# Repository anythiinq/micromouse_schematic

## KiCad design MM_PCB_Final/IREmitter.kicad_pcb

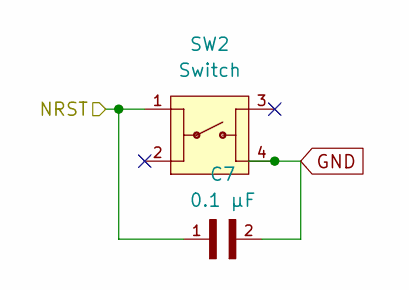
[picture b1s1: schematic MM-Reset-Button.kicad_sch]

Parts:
C7: 0.1 µF; CAPC2012X95N
SW2: Switch; SW_4-1437565-2; PARTREV V

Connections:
/MM-MCU/NRST: C7.1, SW2.1; also elsewhere on the board

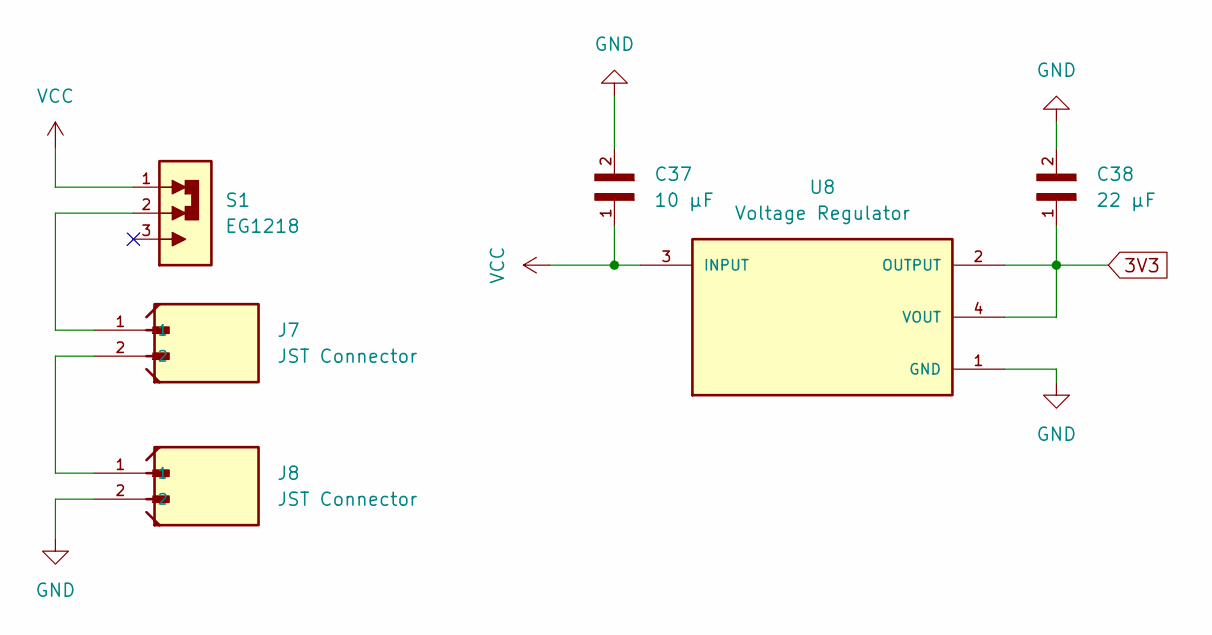
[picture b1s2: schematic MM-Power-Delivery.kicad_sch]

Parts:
C37: 10 µF; CAPC2012X140N
C38: 22 µF; CAPC2012X95N
J7, J8: JST Connector; JST_B2B-PH-K-S
S1: EG1218; SW_EG1218; DigiKey_Part_Number EG1903-ND
U8: Voltage Regulator; SOT230P700X185-4N; PARTREV 2-2

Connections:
3V3: C38.1, U8.2 (OUTPUT), U8.4 (VOUT); also elsewhere on the board
unnamed: J7.1, S1.2
unnamed: J7.2, J8.1
VCC: C37.1, S1.1, U8.3 (INPUT); also elsewhere on the board

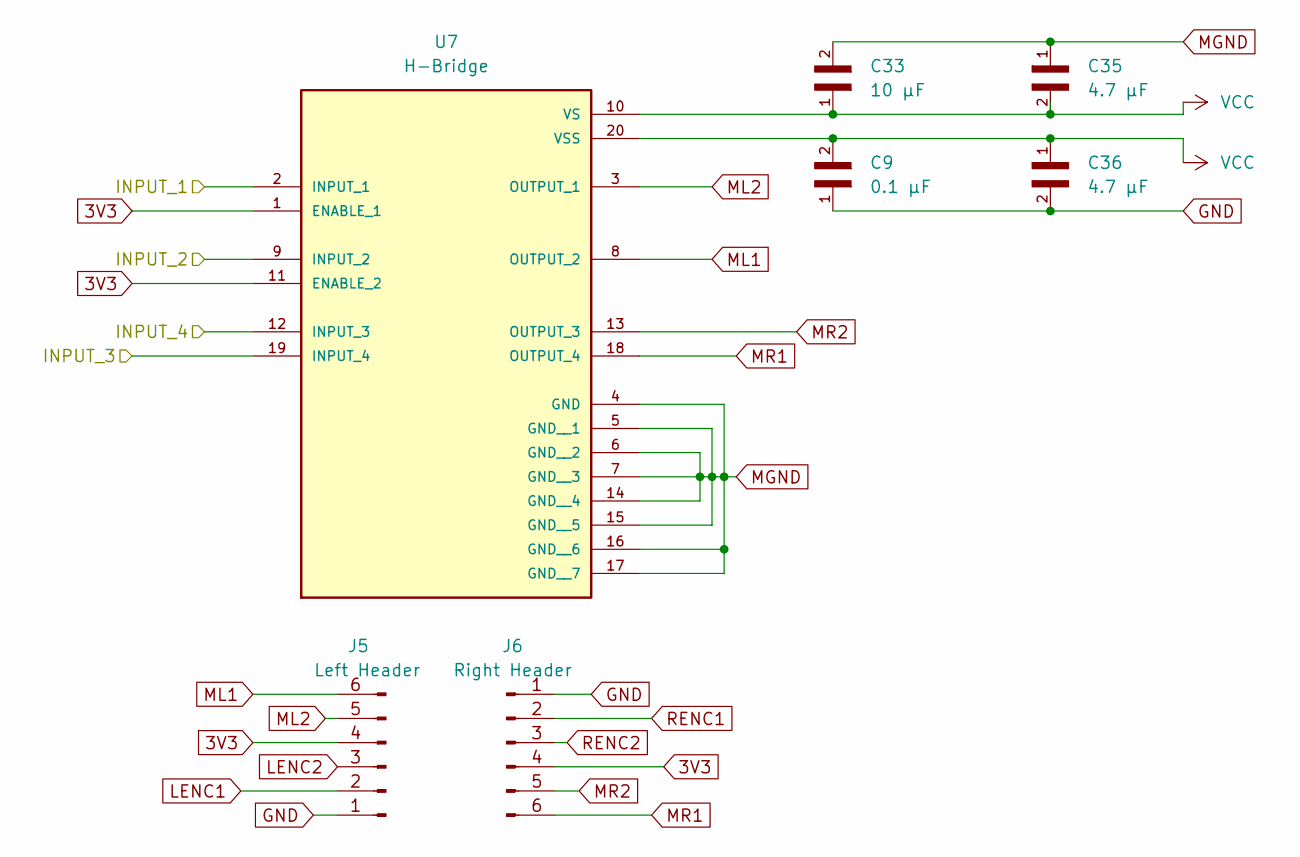
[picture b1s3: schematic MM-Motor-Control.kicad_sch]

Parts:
C9: 0.1 µF; CAPC2012X95N
C33: 10 µF; CAPC2012X140N
C35, C36: 4.7 µF; CAPC2012X140N
J5: Left Header; PinHeader_1x06_P1.27mm_Vertical_SMD_Pin1Left
J6: Right Header; PinHeader_1x06_P1.27mm_Vertical_SMD_Pin1Right
U7: H-Bridge; SOIC127P1032X265-20N; PARTREV N/A

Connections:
3V3: J5.4, J6.4, U7.1 (ENABLE_1), U7.11 (ENABLE_2); also elsewhere on the board
/MM-MCU/INPUT_1: U7.2 (INPUT_1); also elsewhere on the board
/MM-MCU/INPUT_2: U7.9 (INPUT_2); also elsewhere on the board
/MM-MCU/INPUT_3: U7.19 (INPUT_4); also elsewhere on the board
/MM-MCU/INPUT_4: U7.12 (INPUT_3); also elsewhere on the board
ML1: J5.6, U7.8 (OUTPUT_2); also elsewhere on the board
ML2: J5.5, U7.3 (OUTPUT_1); also elsewhere on the board
MR1: J6.6, U7.18 (OUTPUT_4); also elsewhere on the board
MR2: J6.5, U7.13 (OUTPUT_3); also elsewhere on the board
VCC: C9.2, C33.1, C35.2, C36.1, U7.10 (VS), U7.20 (VSS); also elsewhere on the board

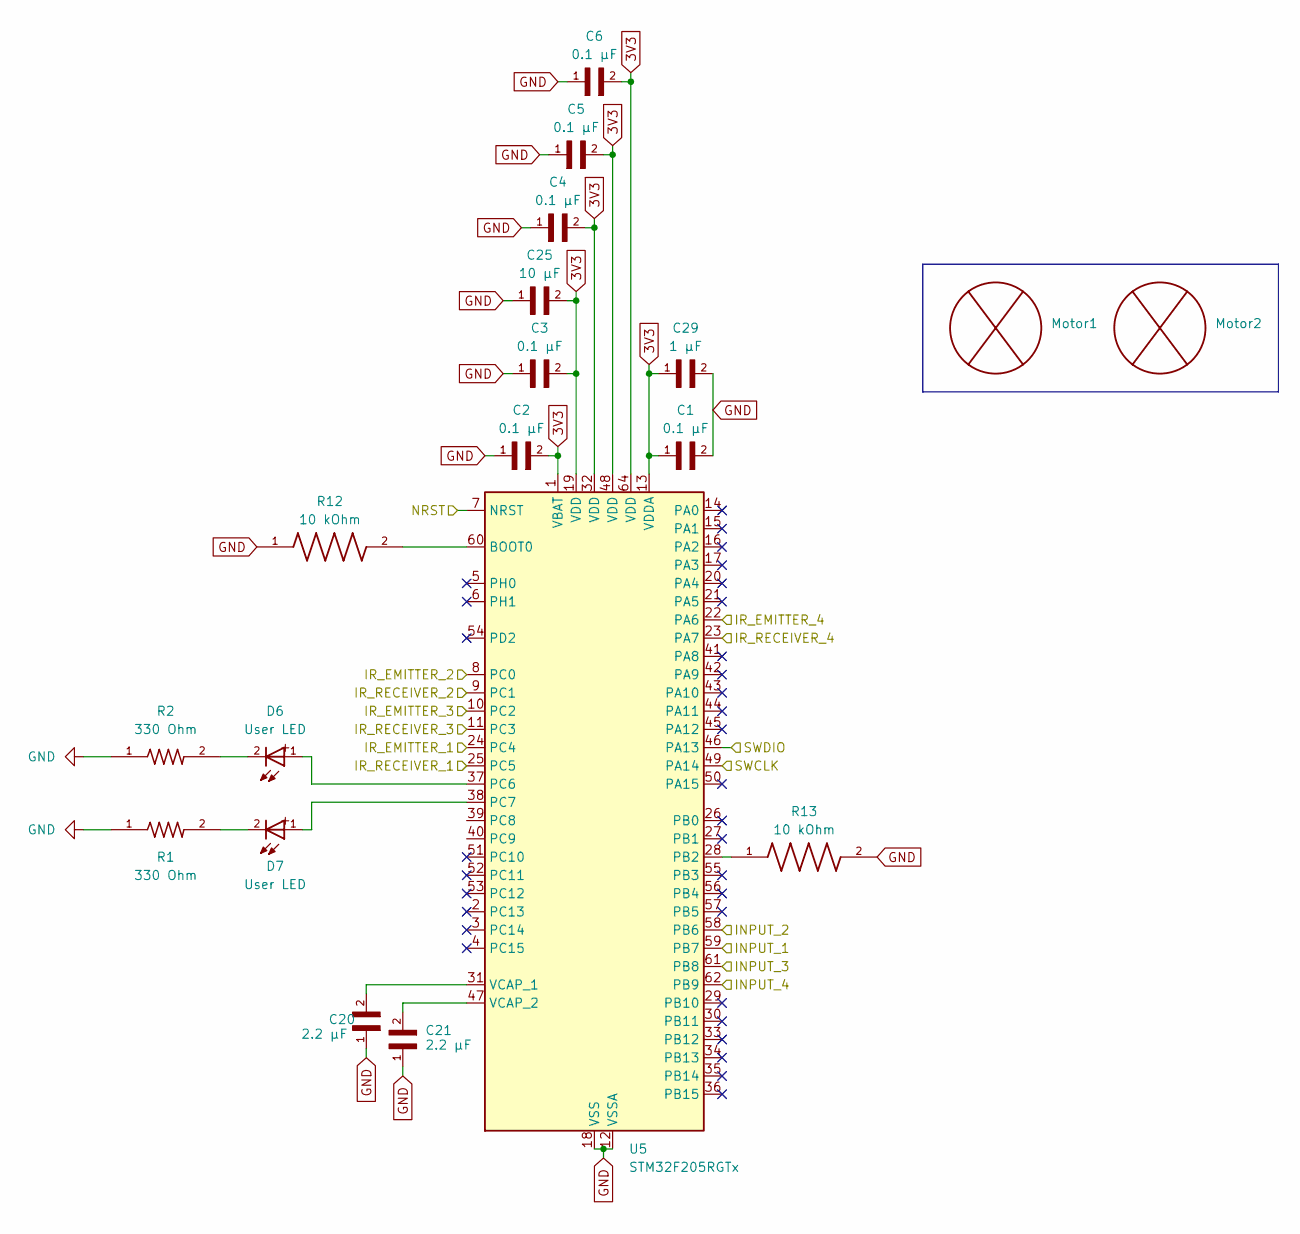
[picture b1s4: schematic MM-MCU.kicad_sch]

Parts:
C1, C2, C3, C4, C5, C6: 0.1 µF; CAPC2012X95N
C20, C21: 2.2 µF; CAPC2012X140N
C25: 10 µF; CAPC2012X140N
C29: 1 µF; CAPC1608X90N
D6, D7: User LED; WL-TMRC_5MM
Motor1, Motor2: Pololu_Motor
R1, R2: 330 Ohm; RESC1607X60N; DigiKey_Part_Number 311-330HRCT-ND
R12, R13: 10 kOhm; RESC2012X65N
U5: STM32F205RGTx; LQFP-64_10x10mm_P0.5mm

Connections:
3V3: C1.1, C2.2, C3.2, C4.2, C5.2, C6.2, C25.2, C29.1, U5.1 (VBAT), U5.13 (VDDA), U5.19 (VDD), U5.32 (VDD), U5.48 (VDD), U5.64 (VDD); also elsewhere on the board
/MM-IR-Emitter/IR_EMITTER_1: U5.24 (PC4); also elsewhere on the board
/MM-IR-Emitter/IR_EMITTER_2: U5.8 (PC0); also elsewhere on the board
/MM-IR-Emitter/IR_EMITTER_3: U5.10 (PC2); also elsewhere on the board
/MM-IR-Emitter/IR_EMITTER_4: U5.22 (PA6); also elsewhere on the board
/MM-IR-Receiver/IR_RECEIVER_1: U5.25 (PC5); also elsewhere on the board
/MM-IR-Receiver/IR_RECEIVER_2: U5.9 (PC1); also elsewhere on the board
/MM-IR-Receiver/IR_RECEIVER_3: U5.11 (PC3); also elsewhere on the board
/MM-IR-Receiver/IR_RECEIVER_4: U5.23 (PA7); also elsewhere on the board
/MM-MCU/INPUT_1: U5.59 (PB7); also elsewhere on the board
/MM-MCU/INPUT_2: U5.58 (PB6); also elsewhere on the board
/MM-MCU/INPUT_3: U5.61 (PB8); also elsewhere on the board
/MM-MCU/INPUT_4: U5.62 (PB9); also elsewhere on the board
/MM-MCU/NRST: U5.7 (NRST); also elsewhere on the board
/MM-MCU/SWCLK: U5.49 (PA14); also elsewhere on the board
/MM-MCU/SWDIO: U5.46 (PA13); also elsewhere on the board
unnamed: D6.2, R2.2
unnamed: D7.2, R1.2
unnamed: R12.2, U5.60 (BOOT0)
unnamed: R13.1, U5.28 (PB2)
unnamed: D6.1, U5.37 (PC6)
unnamed: D7.1, U5.38 (PC7)
unnamed: C20.2, U5.31 (VCAP_1)
unnamed: C21.2, U5.47 (VCAP_2)

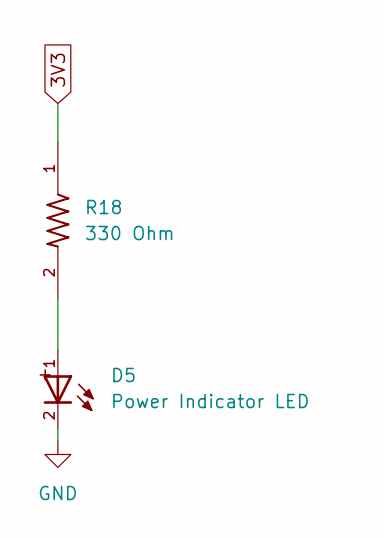
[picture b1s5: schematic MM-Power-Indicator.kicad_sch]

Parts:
D5: Power Indicator LED; WL-TMRC_5MM
R18: 330 Ohm; RESC1607X60N; DigiKey_Part_Number 311-330HRCT-ND

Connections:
3V3: R18.1; also elsewhere on the board
unnamed: D5.1, R18.2

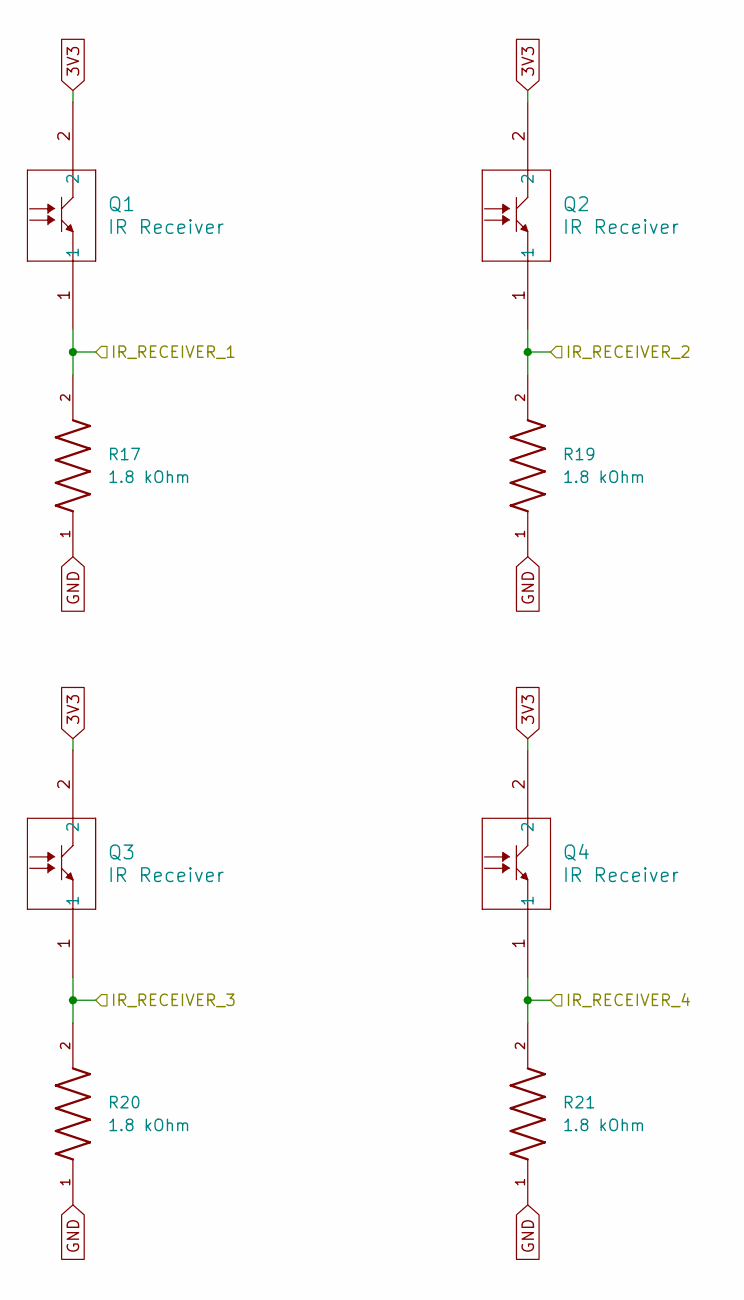
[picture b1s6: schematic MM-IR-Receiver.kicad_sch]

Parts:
Q1, Q2, Q3, Q4: IR Receiver; NoneP157X157-2_LTO
R17, R19, R20, R21: 1.8 kOhm; RESC2012X65N

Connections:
3V3: Q1.2, Q2.2, Q3.2, Q4.2; also elsewhere on the board
/MM-IR-Receiver/IR_RECEIVER_1: Q1.1, R17.2; also elsewhere on the board
/MM-IR-Receiver/IR_RECEIVER_2: Q2.1, R19.2; also elsewhere on the board
/MM-IR-Receiver/IR_RECEIVER_3: Q3.1, R20.2; also elsewhere on the board
/MM-IR-Receiver/IR_RECEIVER_4: Q4.1, R21.2; also elsewhere on the board

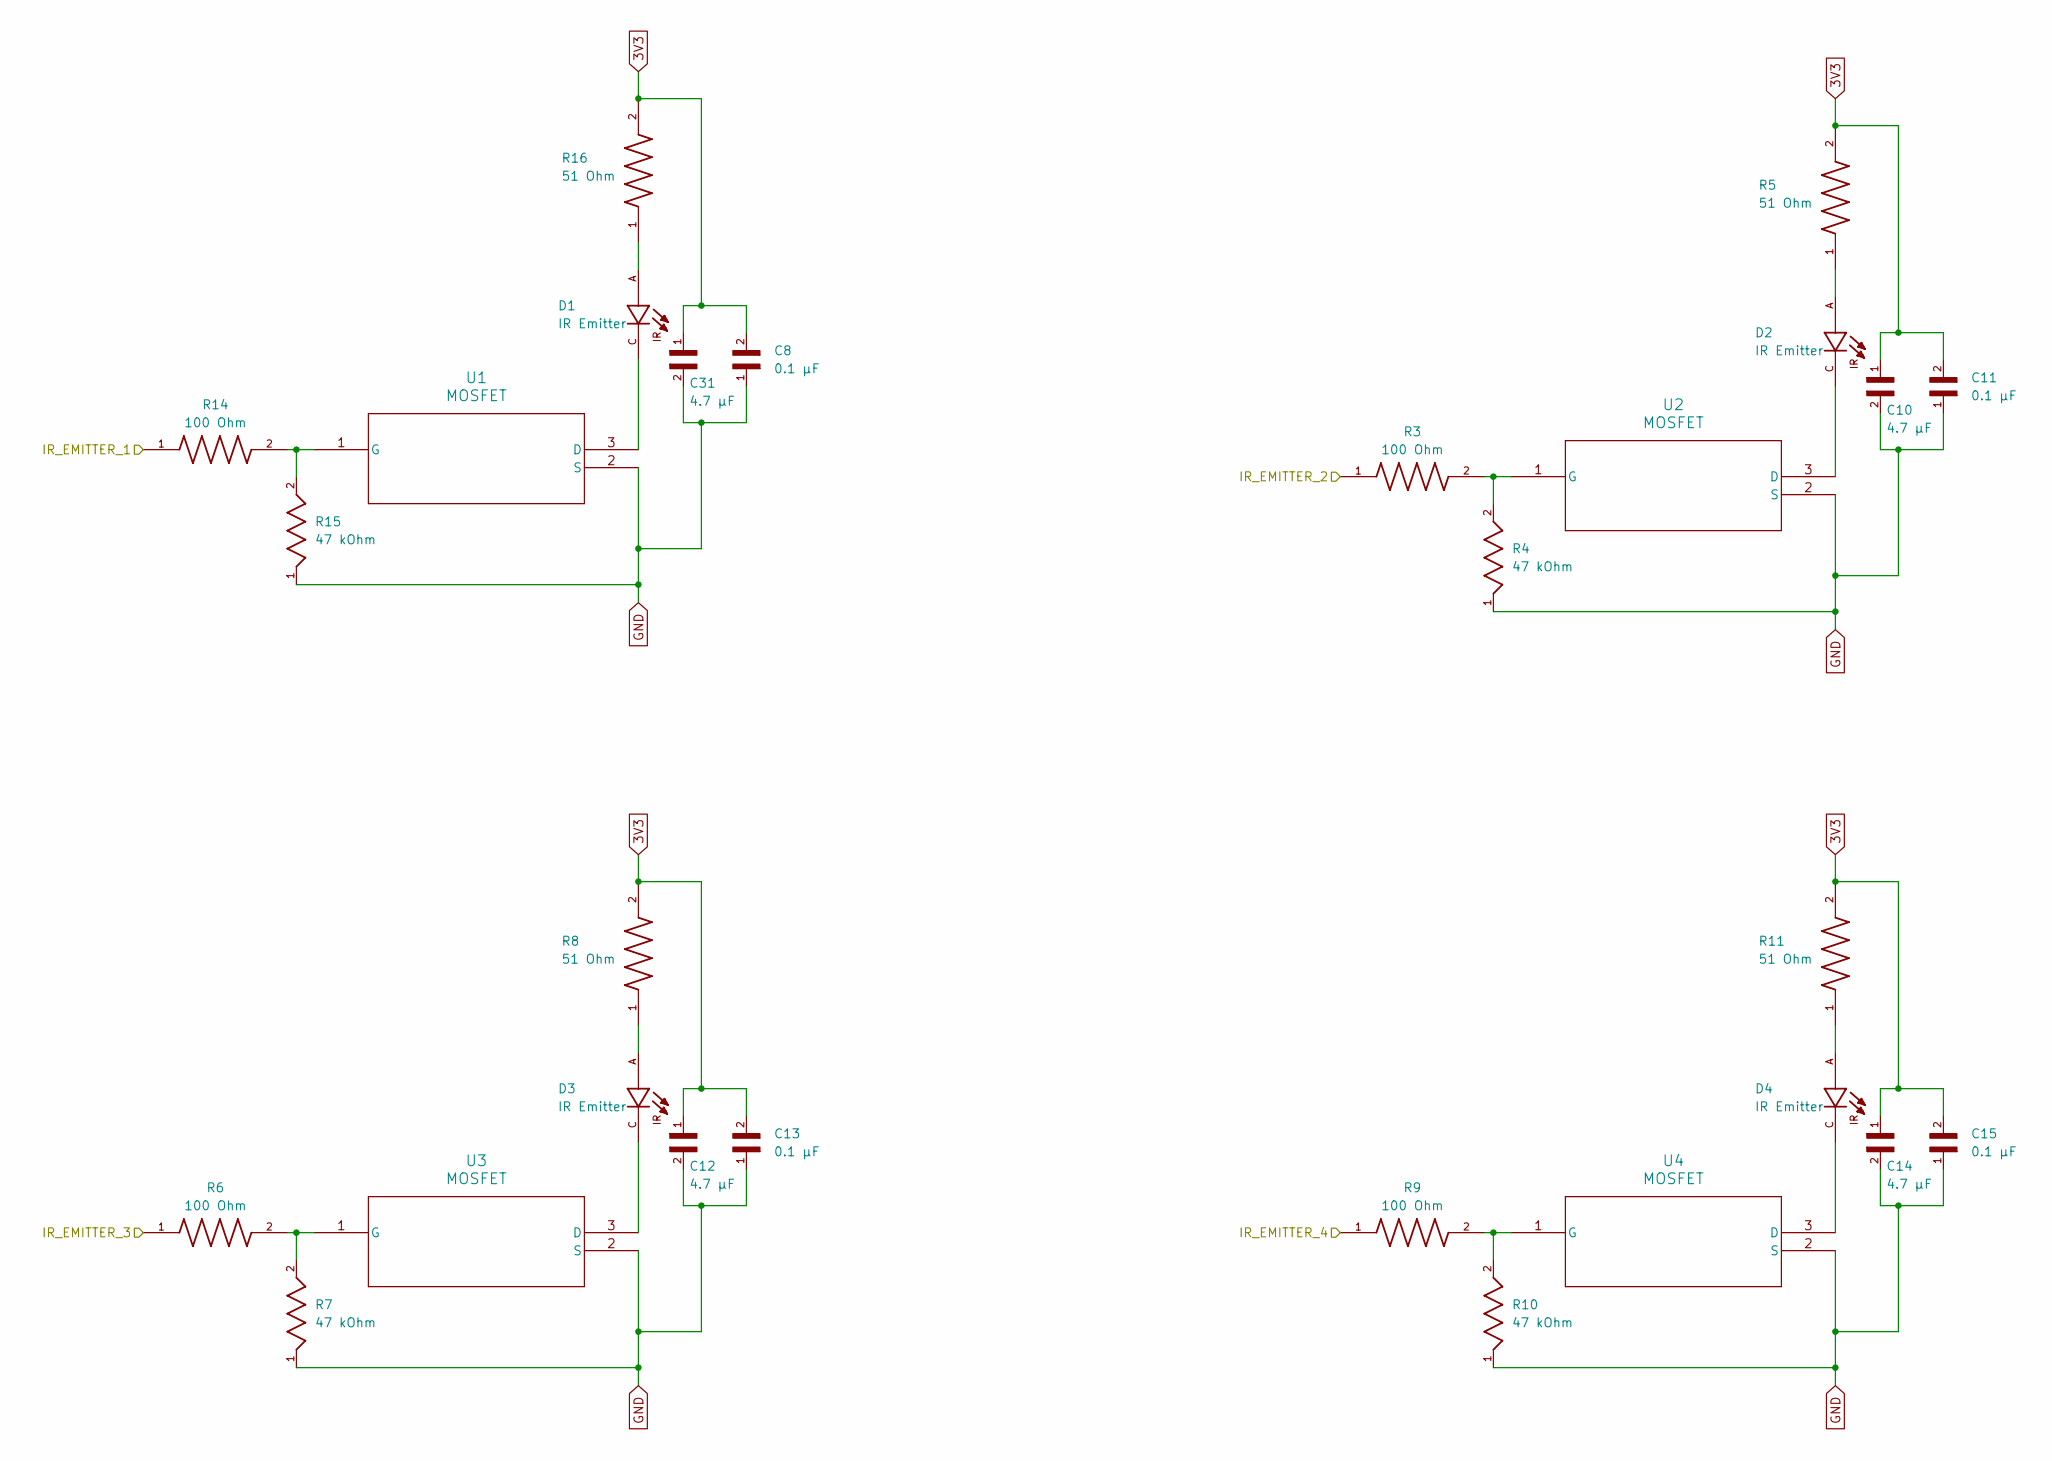
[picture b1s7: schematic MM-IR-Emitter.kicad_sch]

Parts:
C8, C11, C13, C15: 0.1 µF; CAPC2012X95N
C10, C12, C14, C31: 4.7 µF; CAPC2012X140N
D1, D2, D3, D4: IR Emitter; LEDRD254W55D595H900; PARTREV 2.0; DigiKey_Part_Number 751-1205-ND
R3, R6, R9, R14: 100 Ohm; RESC1508X50N
R4, R7, R10, R15: 47 kOhm; RESC1608X55
R5, R8, R11, R16: 51 Ohm; RESC2012X60N
U1, U2, U3, U4: MOSFET; SOT-23_1_DIO

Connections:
3V3: C8.2, C10.1, C11.2, C12.1, C13.2, C14.1, C15.2, C31.1, R5.2, R8.2, R11.2, R16.2; also elsewhere on the board
/MM-IR-Emitter/IR_EMITTER_1: R14.1; also elsewhere on the board
/MM-IR-Emitter/IR_EMITTER_2: R3.1; also elsewhere on the board
/MM-IR-Emitter/IR_EMITTER_3: R6.1; also elsewhere on the board
/MM-IR-Emitter/IR_EMITTER_4: R9.1; also elsewhere on the board
unnamed: D1.A, R16.1
unnamed: D2.A, R5.1
unnamed: D3.A, R8.1
unnamed: D4.A, R11.1
unnamed: D1.C, U1.3 (D)
unnamed: R14.2, R15.2, U1.1 (G)
unnamed: D2.C, U2.3 (D)
unnamed: R3.2, R4.2, U2.1 (G)
unnamed: D3.C, U3.3 (D)
unnamed: R6.2, R7.2, U3.1 (G)
unnamed: D4.C, U4.3 (D)
unnamed: R9.2, R10.2, U4.1 (G)

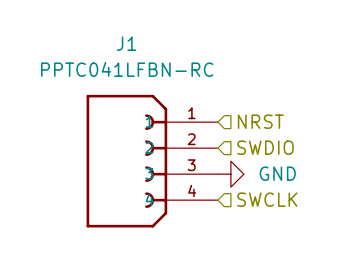
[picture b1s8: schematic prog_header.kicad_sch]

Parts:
J1: PPTC041LFBN-RC; SULLINS_PPTC041LFBN-RC; PARTREV J - 04/15/2015; DigiKey_Part_Number S7002-ND

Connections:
/MM-MCU/NRST: J1.1; also elsewhere on the board
/MM-MCU/SWCLK: J1.4; also elsewhere on the board
/MM-MCU/SWDIO: J1.2; also elsewhere on the board

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
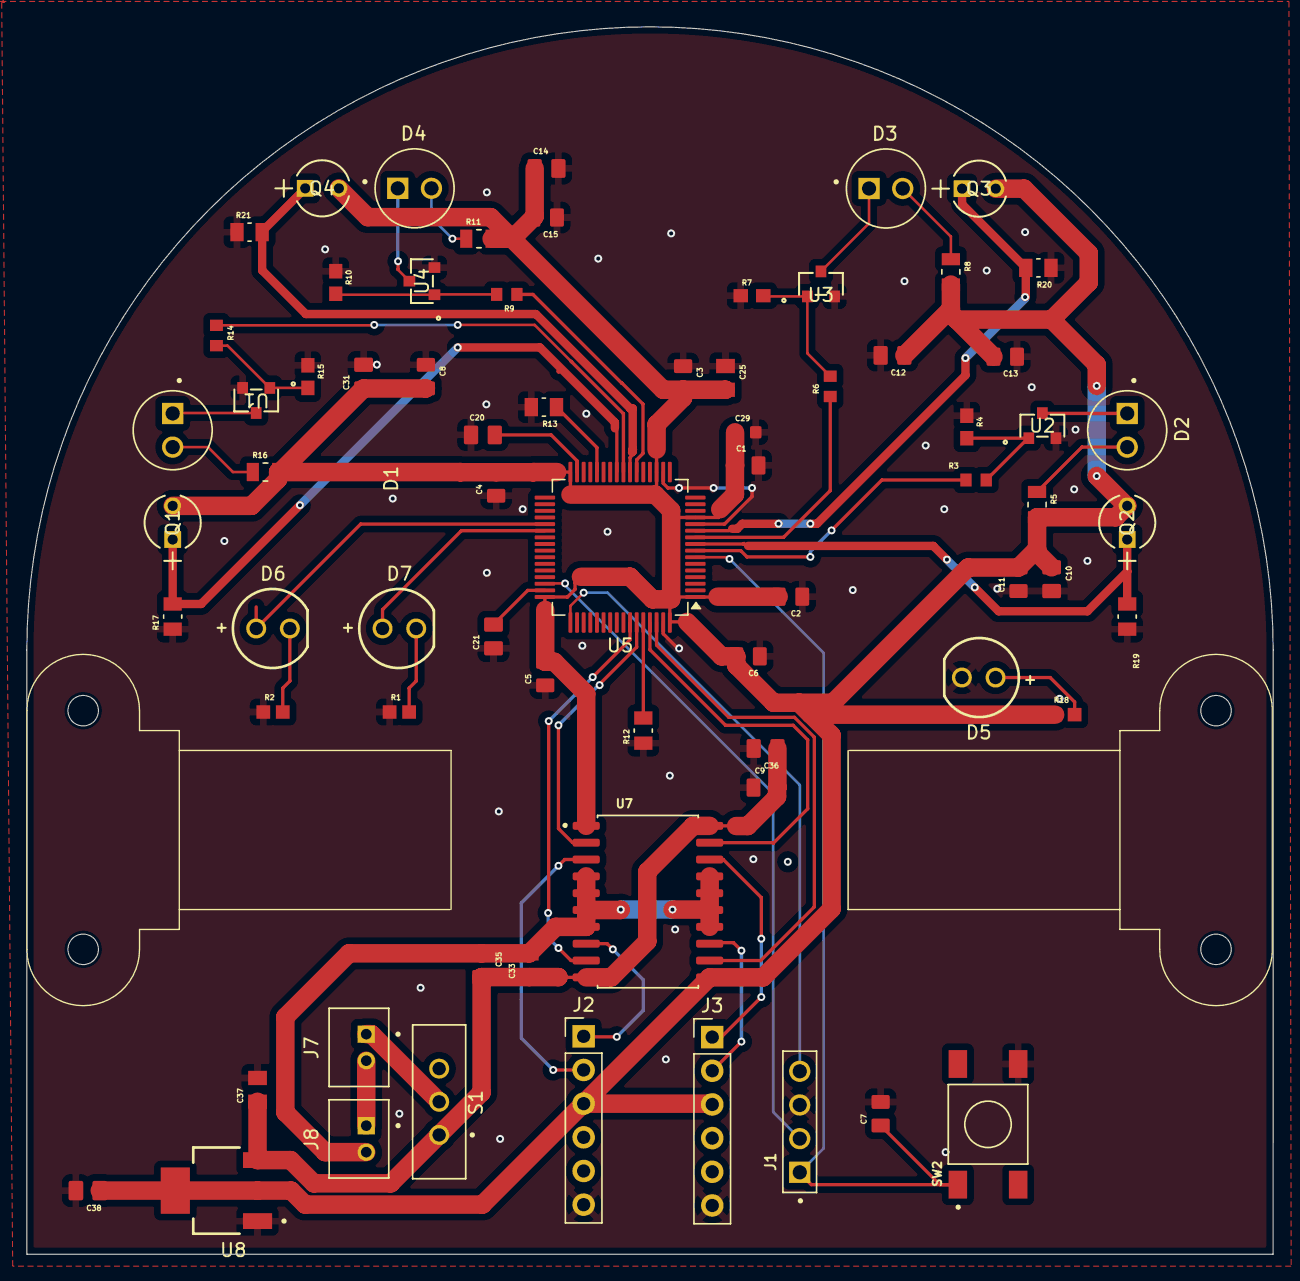
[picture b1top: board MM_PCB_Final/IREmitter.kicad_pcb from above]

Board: 2 copper layers, 94.0 x 92.6 mm, 73 parts (0 on the bottom side), 46 nets.

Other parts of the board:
J2, J3: Conn_01x06; PinHeader_1x06_P2.54mm_Vertical

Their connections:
3V3: J2.3, J3.3; also elsewhere on the board
ML1: J2.1; also elsewhere on the board
ML2: J2.2; also elsewhere on the board
MR1: J3.1; also elsewhere on the board
MR2: J3.2; also elsewhere on the board

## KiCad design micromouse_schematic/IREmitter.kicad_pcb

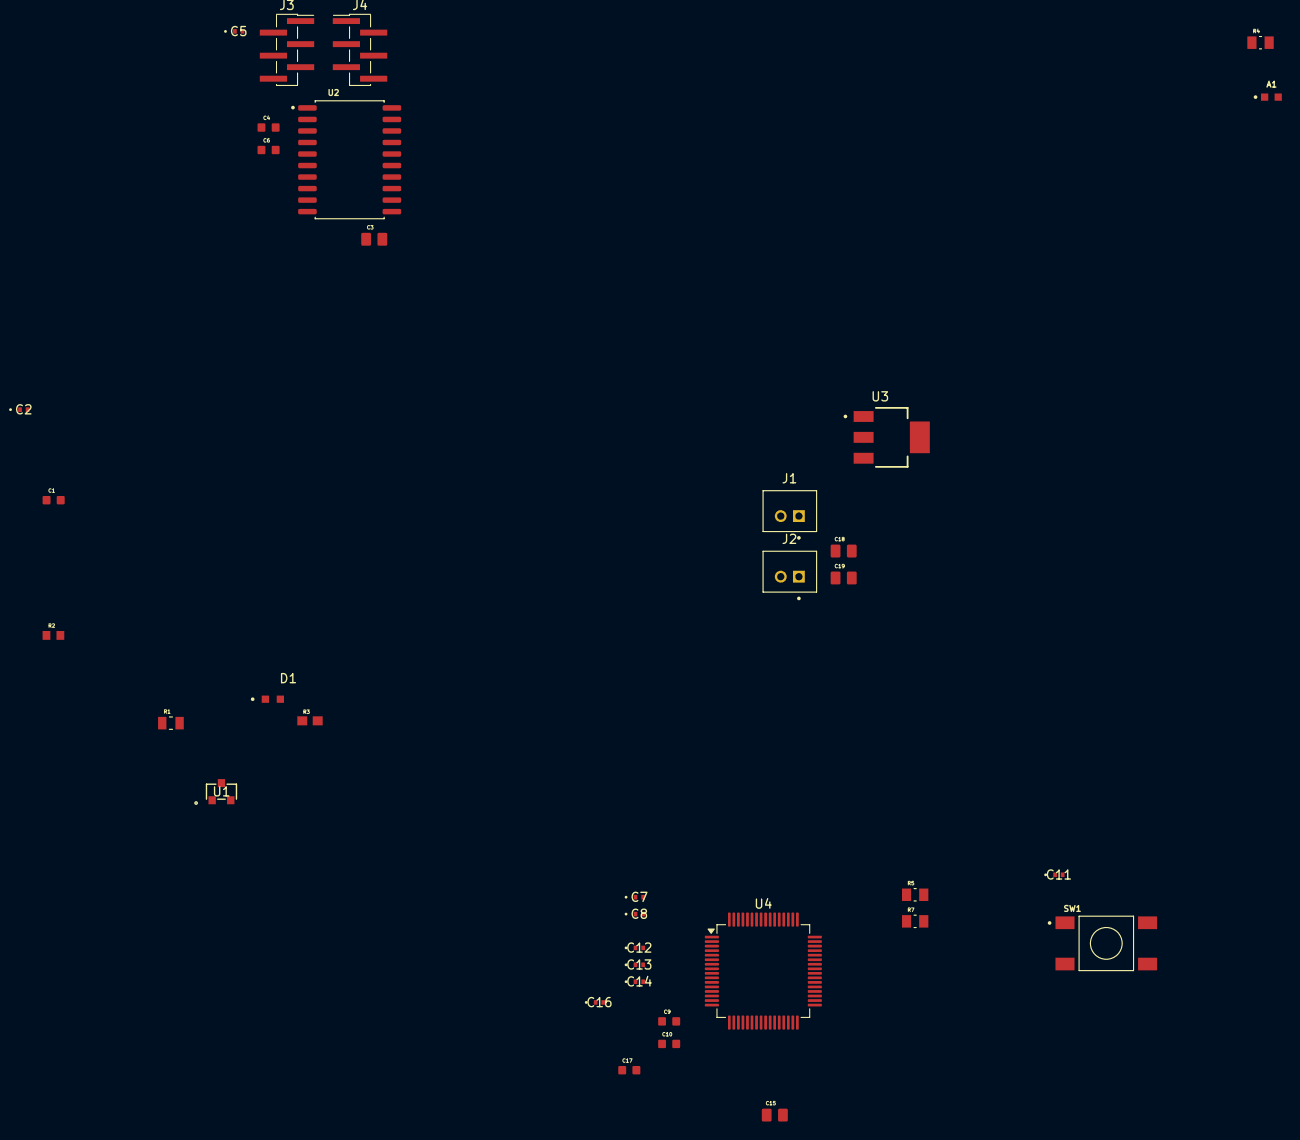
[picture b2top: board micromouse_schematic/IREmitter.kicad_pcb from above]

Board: 2 copper layers, 36 parts (0 on the bottom side), 18 nets, no tracks yet.

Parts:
A1: IR Receiver; XDCR_ALS-PT19-315C_L177_TR8
C1, C4, C6: 4.7 µF; CAPC1608X90N
C2, C5, C7, C8, C12, C13, C14, C16: 0.1 µF; CAP_0402_N_WAL-L
C3, C15, C18: 10 µF; CAPC2012X140N
C9, C10: 2.2 µF; CAPC1608X90N
C11: 0.1 uF; CAP_0402_N_WAL-L
C17: 1 µF; CAPC1608X90N
C19: 22 µF; CAPC2012X140N
D1: IR Emitter; LED_APT1608F3C
J1, J2: JST Connector; JST_B2B-PH-K-S
J3: Right Header; PinHeader_1x06_P1.27mm_Vertical_SMD_Pin1Right
J4: Left Header; PinHeader_1x06_P1.27mm_Vertical_SMD_Pin1Left
R1: 51 Ohm; RESC2012X60N
R2: 100 Ohm; RESC1508X50N
R3: 47 kOhm; RESC1608X55
R4: RMCF0805JT1K80; RESC2012X65N
R5, R7: 10 kOhm; RESC2012X65N
SW1: Switch; SW_4-1437565-2
U1: MOSFET; SOT-23_1_DIO
U2: H-Bridge; SOIC127P1032X265-20N
U3: Voltage Regulator; SOT230P700X185-4N
U4: STM32F205RGTx; LQFP-64_10x10mm_P0.5mm

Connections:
3V3: A1.1, C1.1, C2.2, C7.2, C8.2, C12.2, C13.2, C14.2, C15.2, C16.1, C17.1, C19.1, J3.4, J4.4, R1.2, U2.1 (ENABLE_1), U2.11 (ENABLE_2), U3.2 (OUTPUT), U3.4 (VOUT), U4.1 (VBAT), U4.13 (VDDA), U4.19 (VDD), U4.32 (VDD), U4.48 (VDD), U4.64 (VDD)
GND: C1.2, C2.1, C5.1, C6.2, C7.1, C8.1, C9.1, C10.1, C11.2, C12.1, C13.1, C14.1, C15.1, C16.2, C17.2, C18.2, C19.2, J2.2, J3.1, J4.1, R3.1, R4.1, R5.1, R7.2, SW1.4, U1.2 (S), U3.1 (GND), U4.12 (VSSA), U4.18 (VSS), U4.63 (VSS)
MGND: C3.2, C4.1, U2.4 (GND), U2.5 (GND__1), U2.6 (GND__2), U2.7 (GND__3), U2.14 (GND__4), U2.15 (GND__5), U2.16 (GND__6), U2.17 (GND__7)
ML1: J4.6, U2.8 (OUTPUT_2)
ML2: J4.5, U2.3 (OUTPUT_1)
MR1: J3.6, U2.18 (OUTPUT_4)
MR2: J3.5, U2.13 (OUTPUT_3)
NRST: C11.1, SW1.1, U4.7 (NRST)
unnamed: D1.2, R1.1
unnamed: J1.2, J2.1
unnamed: D1.1, U1.3 (D)
unnamed: R2.2, R3.2, U1.1 (G)
unnamed: R5.2, U4.60 (BOOT0)
unnamed: R7.1, U4.28 (PB2)
unnamed: C9.2, U4.31 (VCAP_1)
unnamed: C10.2, U4.47 (VCAP_2)
PC5 (to be assigned): A1.2, R4.2
VCC: C3.1, C4.2, C5.2, C6.1, C18.1, J1.1, U2.10 (VS), U2.20 (VSS), U3.3 (INPUT)

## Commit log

2026-01-27 Reorganized schematics into a sheet hierarchy
2026-01-28 added basic connections to root page
2026-01-28 added power switch
2026-01-29 fixedled orignetation and linked to ground + duplicated IR emitter/receiver pairs
2026-03-01 redid the 4 emitters receivers, fixed orientation of LEDS and going to continue adding footprints and replace the 60ohm resistors with 300ohm ones
2026-03-01 finished adding rest of footprints, tried replacing mosfets with no success
2026-03-02 LED changes, mosfet footprint fixed
2026-03-08 PCB tentative finished
2026-03-09 finished edits on PCB - hopefully final
2026-03-09 fix mgnd and gnd short
